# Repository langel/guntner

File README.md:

guntner
=====

my first NES game! :D/

release notes

v1.2 - a real title screen and screen garbage clean up

v1.1 - now with sfx and generative music

v1.0 - initial submission to 2020-21 NESDev Compo

[Open this project in 8bitworkshop](http://8bitworkshop.com/redir.html?platform=nes&githubURL=https%3A%2F%2Fgithub.com%2Flangel%2Fguntner&file=guntner.dasm).

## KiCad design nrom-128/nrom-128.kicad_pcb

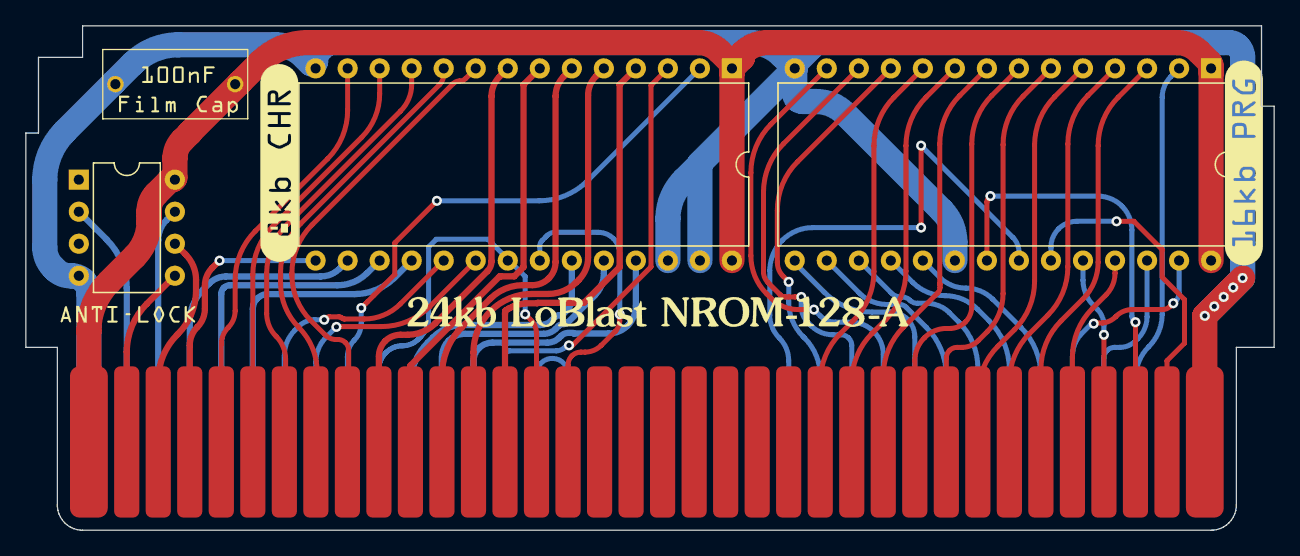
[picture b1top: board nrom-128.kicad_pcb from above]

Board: 2 copper layers, 99.0 x 40.0 mm, 10 parts (0 on the bottom side), 54 nets.

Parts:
C1: 100nF; film-cap
J1: NES_Cart_Edge; NES_Cart_edge
U1: 8kb CHR; DIP-28_W15.24mm
U2: 16kb PRG; DIP-28_W15.24mm
U3: Anti-Lock; DIP-8_W7.62mm
kibuzzard-63F70D0C: G***; kibuzzard-63F70D0C
kibuzzard-63F70D54: G***; kibuzzard-63F70D54
kibuzzard-63F70D89: G***; kibuzzard-63F70D89
kibuzzard-63F711A0: G***; kibuzzard-63F711A0
kibuzzard-63F7105E: G***; kibuzzard-63F7105E

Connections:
/CHR_A0: J1.29 (PPU_A0), U1.10 (A0)
/CHR_A1: J1.28 (PPU_A1), U1.9 (A1)
/CHR_A2: J1.27 (PPU_A2), U1.8 (A2)
/CHR_A3: J1.26 (PPU_A3), U1.7 (A3)
/CHR_A4: J1.25 (PPU_A4), U1.6 (A4)
/CHR_A5: J1.24 (PPU_A5), U1.5 (A5)
/CHR_A6: J1.23 (PPU_A6), U1.4 (A6)
/CHR_A7: J1.59 (PPU_A7), U1.3 (A7)
/CHR_A8: J1.60 (PPU_A8), U1.25 (A8)
/CHR_A9: J1.61 (PPU_A9), U1.24 (A9)
/CHR_A10: J1.22 (CIRAM_A10), J1.63 (PPU_A10), U1.21 (A10)
/CHR_A11: J1.62 (PPU_A11), U1.23 (A11)
/CHR_A12: J1.64 (PPU_A12), U1.2 (A12)
/CHR_CE: J1.65 (PPU_A13), U1.20 (~CE)
/CHR_D0: J1.30 (PPU_D0), U1.11 (D0)
/CHR_D1: J1.31 (PPU_D1), U1.12 (D1)
/CHR_D2: J1.32 (PPU_D2), U1.13 (D2)
/CHR_D3: J1.33 (PPU_D3), U1.15 (D3)
/CHR_D4: J1.69 (PPU_D4), U1.16 (D4)
/CHR_D5: J1.68 (PPU_D5), U1.17 (D5)
/CHR_D6: J1.67 (PPU_D6), U1.18 (D6)
/CHR_D7: J1.66 (PPU_D7), U1.19 (D7)
/CHR_OE: J1.21 (PPU_~RD), U1.22 (~OE)
/CIC_CLK: J1.71 (CIC_CLK), U3.2 (PB3)
/CIC_IN: J1.34 (CIC_toPak), U3.6 (PB1)
/CIC_OUT: J1.35 (CIC_toMB), U3.5 (PB0)
/CIC_RST: J1.70 (CIC_+RST), U3.7 (PB2)
/PRG_A0: J1.13 (CPU_A0), U2.10 (A0)
/PRG_A1: J1.12 (CPU_A1), U2.9 (A1)
/PRG_A2: J1.11 (CPU_A2), U2.8 (A2)
/PRG_A3: J1.10 (CPU_A3), U2.7 (A3)
/PRG_A4: J1.09 (CPU_A4), U2.6 (A4)
/PRG_A5: J1.08 (CPU_A5), U2.5 (A5)
/PRG_A6: J1.07 (CPU_A6), U2.4 (A6)
/PRG_A7: J1.06 (CPU_A7), U2.3 (A7)
/PRG_A8: J1.05 (CPU_A8), U2.25 (A8)
/PRG_A9: J1.04 (CPU_A9), U2.24 (A9)
/PRG_A10: J1.03 (CPU_A10), U2.21 (A10)
/PRG_A11: J1.02 (CPU_A11), U2.23 (A11)
/PRG_A12: J1.39 (CPU_A12), U2.2 (A12)
/PRG_A13: J1.40 (CPU_A13), U2.26 (A13)
/PRG_A14: J1.41 (CPU_A14), U2.27 (A14)
/PRG_D0: J1.49 (CPU_D0), U2.11 (D0)
/PRG_D1: J1.48 (CPU_D1), U2.12 (D1)
/PRG_D2: J1.47 (CPU_D2), U2.13 (D2)
/PRG_D3: J1.46 (CPU_D3), U2.15 (D3)
/PRG_D4: J1.45 (CPU_D4), U2.16 (D4)
/PRG_D5: J1.44 (CPU_D5), U2.17 (D5)
/PRG_D6: J1.43 (CPU_D6), U2.18 (D6)
/PRG_D7: J1.42 (CPU_D7), U2.19 (D7)
/PRG_OE: J1.50 (~ROMSEL), U2.22 (~OE)
GND: C1.2, J1.01 (GND), J1.72 (GND), U1.14 (GND), U1.26 (A13), U1.27 (A14), U2.14 (GND), U2.20 (~CE), U3.4 (GND)
unnamed: J1.57 (CIRAM_~CE), J1.58 (PPU_~A13)
VCC: C1.1, J1.36 (+5V), U1.1 (A15), U1.28 (VCC), U2.1 (A15), U2.28 (VCC), U3.8 (VCC)

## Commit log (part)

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2022-02-11 hex scoreboard logic
2022-02-11 char rom better for hex display
2022-02-12 new lifebar drawing code
2022-02-12 removed unused files
2022-02-12 oh thats how char roms work i guess
2022-02-12 refactor bug fixes
2022-02-12 lifebar and constant names fixings
2022-02-13 starting to count PPU write cycles
2022-02-14 starfield update using INC_32 on PPU
2022-02-14 (re)moved sprites and tiles
2022-02-14 dashboard hella smoove
2022-02-15 new palette handler
2022-02-15 fade in fade out kind of working
2022-02-16 optimized control reading and misc
2022-02-16 will state machine save us
2022-02-17 palette and scroll_x fixed
2022-02-17 fixed title screen palette rotation
2022-02-17 menu screens using new state machine
2022-02-17 almost done with state machine conversion
2022-02-18 some bugs but state machine is in
2022-02-18 lots of nametable attr tweaks
2022-02-18 sprite0 y in cart start
2022-02-18 bullets in zp
2022-02-18 caching next enemy slots below sprite0
2022-02-18 some tile work
2022-02-18 starfield death wind down stability
2022-02-18 game hardening
2022-02-19 added dumbface
2022-02-22 updated sandbox and dumb face
2022-02-22 having some fun
2022-02-23 upwards text animation
2022-02-23 2 seconds of invincibility frames
2022-02-24 struggling with sine scaler
2022-02-24 fixed sine scaler's bad scaling
2022-02-26 starfield transitions almost oh no
2022-02-26 starfield from bg to sprite
2022-02-26 renamed boss_v array to state_v
2022-02-27 starfield transition frames are awful
2022-03-02 what a mess
2022-03-02 only init stars bg2spr once
2022-03-02 starfield transition loop unlocked
2022-03-03 can darts go in angles
2022-03-05 inverse tangents really working
2022-03-05 optimized 16bit player movement (carry)
2022-03-05 darts collide with player
2022-03-06 backup of exports and misc
2022-03-17 galactic vampire sprites
2022-03-17 moved arctang to own file/subroutines
2022-03-18 vampire has states
2022-03-19 vampire spawns and dies
2022-03-19 vampire lunge wait rng
2022-03-20 vampire mouth time
2022-03-20 vampire grafx update
2022-03-21 vamp tweaks forever
2022-03-22 vampire basically done
2022-03-22 whats left now
2022-03-23 new logo prep
2022-03-23 new title screen logo is a go
2022-03-23 some powerup sprites
2022-03-24 many new powerups
2022-03-25 bullet refactor and mask shield powerup
2022-03-26 8 powerup behaviours working
2022-03-26 bomb 1 damage every other frame
2022-03-29 bpl for better loops
2022-03-30 sfx expirement
2022-03-30 sine table for audio envelope
2022-04-01 sfx are hard
2022-04-03 wow a song appears
2022-04-04 apu soft enevelopes oh no
2022-04-05 sound is hard
2022-04-06 new audio engine starting to work
2022-04-06 powerup hit still glitchy
2022-04-06 powerup hit envelope fix
2022-04-06 powerup pickup jump table
2022-04-06 sfx variations
2022-04-07 found palette rot apu bug
2022-04-07 small ram schema notes
2022-04-07 bomb powerup feeling done
2022-04-07 mushroom music bend a go
2022-04-08 new shroom movement
2022-04-08 a little cleanup
2022-04-08 moar exports
2022-04-08 demo bugs fixed
2022-04-09 an ant appears
2022-04-12 barbs and darts study
2022-04-13 dartbarb sprites and notes
2022-04-13 darts in 24 directions
2022-04-14 dart understandings
2022-04-14 better dart (de)spawnings
2022-04-15 better iframes and scroll speed caching
2022-04-15 moar starfield state hardening
2022-04-16 moar small tweaks
2022-04-17 ceiling ant better dart origin
2022-04-18 star sprites allow small and large enemies
2022-04-19 enemy dmg/death refactor
2022-04-20 more enemy redundancy reductions
2022-04-21 arctang variable velocities
2022-04-21 vamp boss velocity in yeah
2022-04-21 throber working and other optimizations
2022-04-22 tiny tweaks
2022-04-22 new chomps sprites
2022-04-22 chomps pattern and other bugs
2022-04-22 moar sprites
2022-04-22 chomps in the can
2022-04-22 more ant animation frames
2022-04-23 uzi up in this piece
2022-04-23 a lariot appears
2022-04-23 long rope lasso
2022-04-24 bullet and dart sfx
2022-04-24 better ant butt dart origin placement
2022-04-24 lasso extension adjustments
2022-04-26 scarab sprites
2022-04-27 scarab boss looking good
2022-04-27 better scarab wings
2022-04-27 better scarab wing animation
2022-04-27 turn off boss death flag after boss death process
2022-04-30 2 more flight paths
2022-04-30 flight paths phases in sequential order
2022-04-30 pahse_current modulus flight path
2022-04-30 modularized starfield transition return
2022-05-03 some tweaks
2022-06-10 wide s galger pattern
2022-06-11 galger arcleg refactor
2022-06-11 fixed galger horseshoe loop
2022-06-15 16 arcleg flight paths
2022-06-15 refactoring arc sequence setup
2022-06-15 arc sequence handling refactored
2022-06-15 cycling through arcleg sequences
2022-06-16 arc leg seq demo
2022-06-17 added exports
2022-06-18 new phase engine in the works
2022-06-21 moved menu vars from zp
2022-06-21 filename cleanup
2022-06-21 filename fixes
2022-06-21 level 1 playable
2022-06-22 many subtle scarab boss enhancements
2022-06-22 bug fixes
2022-06-22 moved chr patterns around
2022-06-22 updated level phase debugger
2022-06-23 16bit starfield scroll speeds
2022-06-24 song playback working on options screen
2022-06-24 title chords and mushroom effect in sound options
2022-06-24 a new song appears
2022-06-25 moar stars grafx
2022-06-25 second pause between phases
2022-06-26 fixed audio engine ignoring new notes bug
2022-06-27 more exports
2022-06-28 prep for new string system
2022-06-28 new char set arrangement
2022-06-28 rearranged char rom again
2022-06-28 moved more bg tiles around
2022-06-28 bg tile data updated
2022-06-29 multi endings state setup
2022-06-29 something
2022-06-29 added portraits chr rom
2022-06-29 distressed alien tiles in chr rom
2022-06-30 intro cut scene done
2022-06-30 text chars rearranged again
2022-06-30 difficulty setting in options screen
2022-06-30 optimized option screen input handling
2022-07-01 phase zero implemented
2022-07-02 iframes on shield loss
2022-07-02 fixed spark spawn positions
2022-07-02 maybe fixed mushroom pitch bending
2022-07-02 refactored r bags and lazy turbo
2022-07-02 spark goes right more often than left
2022-07-02 spawning boss on phases Xf
2022-07-03 half refactored phase spawnings
2022-07-03 attract mode refactored spawn code
2022-07-04 more phase handler bugs
2022-07-06 fixed a spawn bug but theres more
2022-07-06 another portrait in the chr
2022-07-07 drawing cut scene end game alien on screen
2022-07-08 reset level palettes after mushroom powerup
2022-07-08 cleaned up a lot of XXX comments
2022-07-09 boss palettes handled by palette system
2022-07-10 boss fight music done
2022-07-10 chr tiles moved around
2022-07-10 handling boss palettes in phase handler
2022-07-10 removed palette code from scarab
2022-07-12 fit another table in top of rom
2022-07-12 spark now has general downward movement
2022-07-12 fixed phase advancement bug
2022-07-13 grayscale on game over
2022-07-13 rescued "sick dingle" song again
2022-07-13 almost in game music
2022-07-14 in game music feels done
2022-07-14 shroom effect working on options screen
2022-07-14 eff bb-8
2022-07-14 fixing xxx comment areas
2022-07-14 return of eff bb-8
2022-07-14 cleaned up player movement comments
2022-07-14 abstracted phase palette logic to single subroutine
2022-07-15 phase tables populated
2022-07-15 2nd quest is boundless
2022-07-15 notes and portraits
2022-07-15 64 phases -- its like a whole game!!
2022-07-16 is it really a game tho
2022-07-16 slight refactor and nerf of enemy damage
2022-07-16 dont spawn while player dead
2022-07-16 new attract mode enemy lineup
2022-07-16 fixed powerups despawning bug
2022-07-30 shrank enemy code
2022-07-30 MOAR shrank enemy code
2022-07-30 fixed zigzag game crashing bug
2022-07-31 fixed endgame returning to title screen
2022-08-01 squoze some more bytes
2022-08-03 big bug fixes
2022-08-03 swordtner sprite and rudy dithered
2022-08-03 moved in game rudy graphics
2022-08-04 swordtner sequence complete
2022-08-04 swordtner LIVES
2022-08-04 muya starting to work
2022-08-04 muya working as intended
2022-08-05 moufs and ikes mom graphics
2022-08-05 lasso spawn x pos bug
2022-08-05 fixed palette fade in process
2022-08-06 moufs on screen
2022-08-06 moufs starting to mouf about
2022-08-06 fixed various boss palette bugs
2022-08-06 moufs movement done
2022-08-07 fixed arctang bounds subroutine
2022-08-07 double checked all arctang velocities are set
2022-08-08 more variables reset for new game
2022-08-09 fixed moufs dart spawns
2022-08-09 refactored scarab sprites saved 66 bytes
2022-08-09 reversed scarab colors fixed sun bullet colors
2022-08-09 clear state function
2022-08-09 fixed contra code
2022-08-10 fixed skullmaskshield turbo cannon death save
2022-08-10 spawn starglasses every 20 seconds
2022-08-10 spawn ikes mom and more starglasses
2022-08-11 updated copyright line / added ax1147
2022-08-12 game ends at 100 minutes / bad ending at 15 minutes
2022-08-12 graphical updates
2022-08-12 some spawn table stats
2022-08-13 bats show on vamp death
2022-08-13 optimized some sprites in the chr rom
2022-08-13 vamp boss really done
2022-08-13 moufs boss animation done
2022-08-14 chomps new y on x wrap
2022-08-14 sprite_0_y vars converted to macros
2022-08-15 palette overhaul and filling outedness
2022-08-15 stars brighter for boss fight; fixed black colors
2022-08-15 fixed rudy direction on menu screens
2022-08-17 enemy death handle refactor in progress
2022-08-17 fixed both death killing all enemies
2022-08-17 added publisher's line to title screen
2022-08-17 fixed powerups despawning after boss fight
2022-08-17 fixed dart despawnings
2022-08-17 vamp boss enhancements/fixes
2022-08-19 mad jump table refactorings
2022-08-19 state handler mega shrinkage
2022-08-19 more jump table conglomerations
2022-08-19 fixed jump table conglomeration bugs
2022-08-19 boss spawn fade from white
2022-08-19 rudy iframe flashing enhancement
2022-08-19 each boss has 2 assistant spawns
2022-08-20 swordtner sucking less
2022-08-21 swordtner has 2 modes wow
2022-08-21 swordtner toggling between modes wow
2022-08-21 crossbones and muya share upwards code
2022-08-22 fixed good ending song bad notes
2022-08-22 adjusted difficulty damage settings
2022-08-22 deleted unused subroutines and tables
2022-08-22 label audit tool
2022-08-22 select + start turns on boundless mode
2022-08-22 better visualization of player damages
2022-08-23 better lesset powerup drop rng
2022-08-23 boss assistants getting proper slots
2022-08-24 optimized/cutup apu engine tables
2022-08-24 options screeen in game music lifebar magic
2022-08-24 removed more state handler functions xD
2022-08-25 bookbinders name appears
2022-08-25 bylines title screen palette atrtibutes
2022-08-25 ikes mom sound effect
2022-08-25 added faster player speed
2022-08-26 optimized play bullet collision handling
2022-08-26 endgame cutscene return error
2022-08-26 swordtner shoot before enemy emissions
2022-08-27 super secret wowow
2022-08-29 orbit shield pos zp var
2022-08-29 use carry to return boolean on enemy slot availabilty
2022-08-31 some last details notes
2022-09-01 saved 4 bytes
2022-09-01 fixed bad sparks spawn y speed
2022-09-02 fixed vamp dead dart bug
2022-09-02 fixed powerup despawn after player death
2022-09-19 swordtner better y bound bounce outs
2022-09-24 cart edge connector symbol
2022-09-24 schematic busses are happening
2022-09-25 nrom 128 board schematic filled out
2023-01-24 PCB net completely routed
2023-01-24 PCB edge connector corrected
2023-01-29 protoboard rev 0
2023-01-30 more space on publishers line
2023-01-30 block turbo cannon on phase 0
2023-01-30 stubbed out title partner bylines
2023-02-08 made room for numbered edition id
2023-02-08 working roms for chips
2023-02-25 manually soldered PCB
2023-03-03 adding dev export roms
2023-03-09 MGC tagline logged
2023-03-15 numbered rom proggie
2023-04-08 notes update
2023-04-25 added 2 vsyncs to startup
2023-04-25 better byte parity with older versions
2023-10-06 added retrostage board writer tool
2025-03-31 scrimp error box byline option
2026-01-05 error box edition rom files
2026-03-04 rough draft of book project
2026-03-08 more book edits
